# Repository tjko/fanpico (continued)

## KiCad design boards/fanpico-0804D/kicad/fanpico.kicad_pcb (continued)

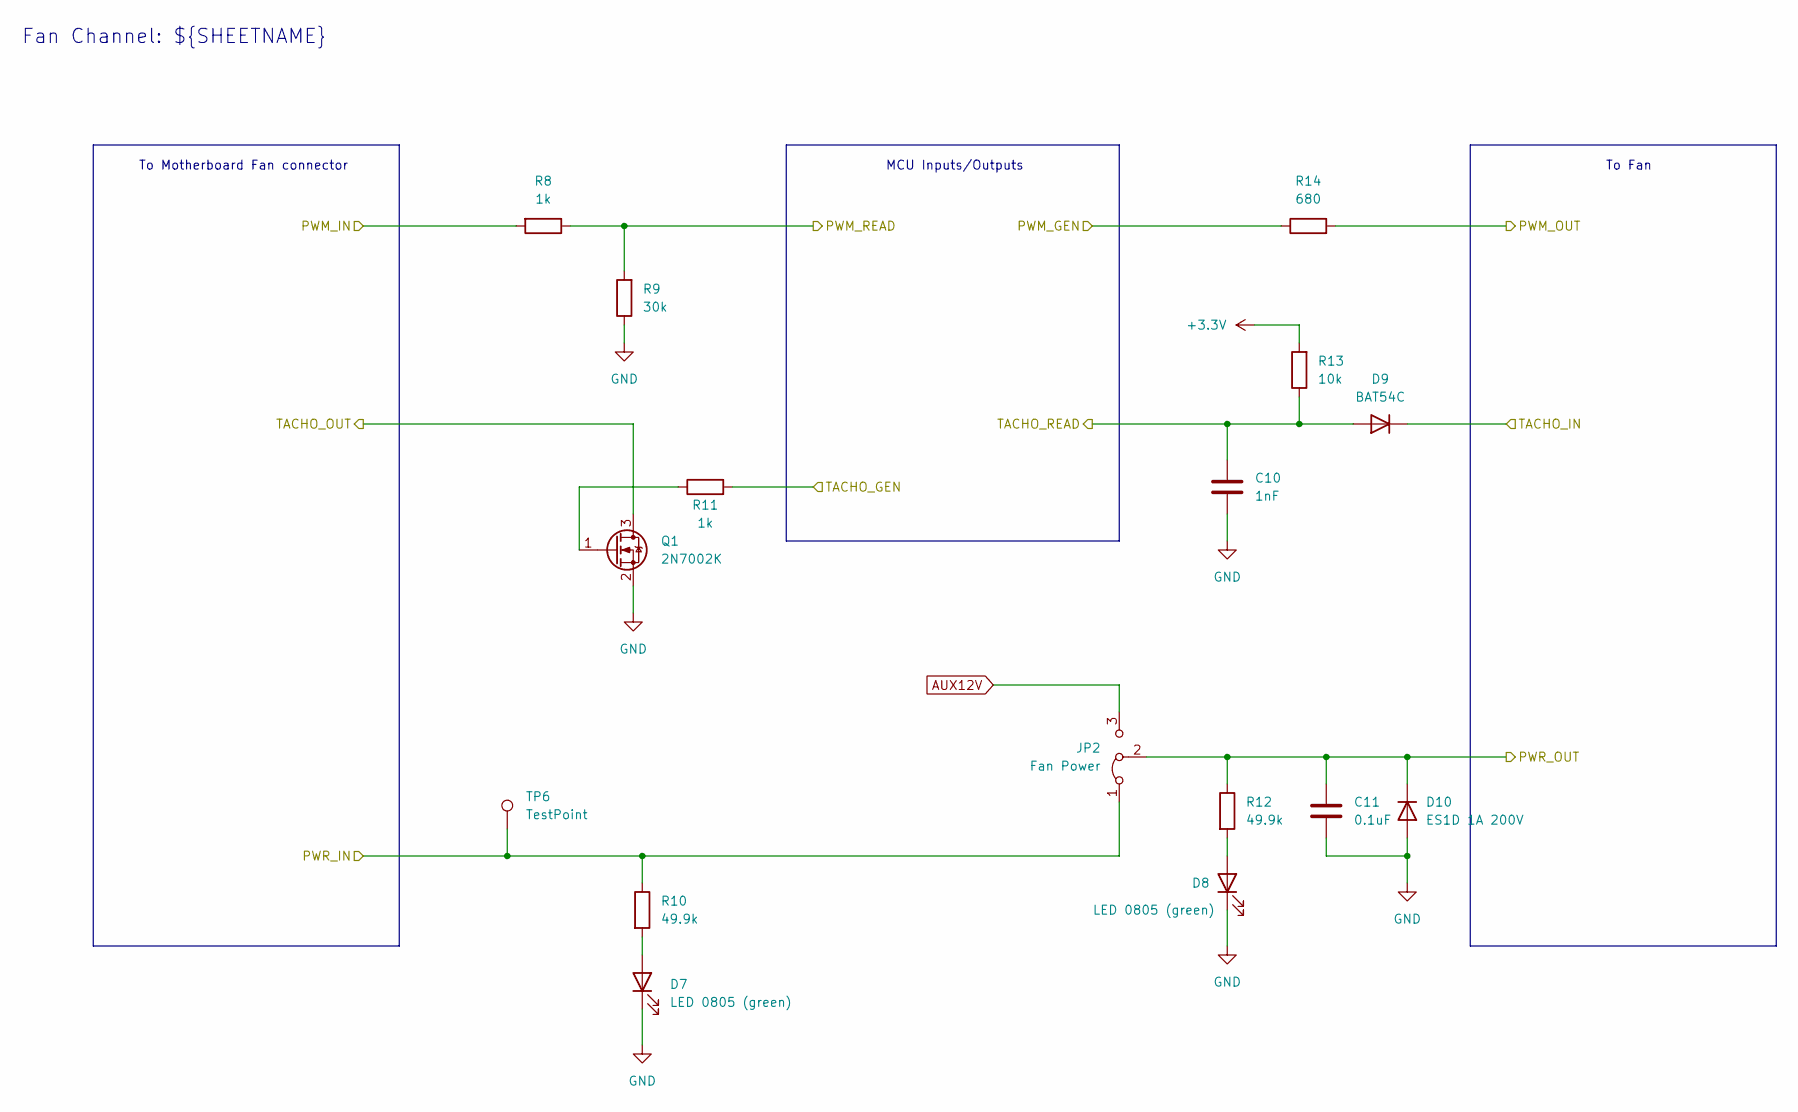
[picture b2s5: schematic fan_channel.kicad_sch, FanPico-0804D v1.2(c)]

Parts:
C10: 1nF; C_0603_1608Metric_Pad1.08x0.95mm_HandSolder; LCSC Part Number C1588
C11: 0.1uF; C_0603_1608Metric_Pad1.08x0.95mm_HandSolder; LCSC Part Number C1591
D7, D8: LED 0805 (green); LED_0805_2012Metric_Pad1.15x1.40mm_HandSolder; LCSC Part Number C434432
D9: BAT54C; D_SOT-23_ANK; LCSC Part Number C2844172
D10: ES1D 1A 200V; D_SMA_Handsoldering; LCSC Part Number C445494
JP2: Fan Power; PinHeader_1x03_P2.54mm_Vertical
Q1: 2N7002K; SOT-23; LCSC Part Number C85047
R8, R11: 1k; R_0603_1608Metric_Pad0.98x0.95mm_HandSolder; LCSC Part Number C22548
R9: 30k; R_0603_1608Metric_Pad0.98x0.95mm_HandSolder; LCSC Part Number C100001
R10, R12: 49.9k; R_0603_1608Metric_Pad0.98x0.95mm_HandSolder; LCSC Part Number C114624
R13: 10k; R_0603_1608Metric_Pad0.98x0.95mm_HandSolder; LCSC Part Number C98220
R14: 680; R_0603_1608Metric_Pad0.98x0.95mm_HandSolder; LCSC Part Number C115415
TP6: TestPoint; TestPoint_Pad_D1.5mm

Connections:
3V3: R13.2; also elsewhere on the board
/Fan Channels/Fan1/PWM_IN: R8.2; also elsewhere on the board
/Fan Channels/Fan1/PWM_OUT: R14.2; also elsewhere on the board
/Fan Channels/Fan1/PWR_OUT: C11.1, D10.1 (K), JP2.2 (C), R12.1; also elsewhere on the board
/Fan Channels/Fan1/TACHO_IN: D9.1 (K); also elsewhere on the board
/Fan Channels/Fan1/TACHO_OUT: Q1.3 (D); also elsewhere on the board
AUX12V: JP2.3 (B); also elsewhere on the board
FAN1_PWM_GEN: R14.1; also elsewhere on the board
FAN1_PWR: JP2.1 (A), R10.1; also elsewhere on the board
FAN1_TACHO_READ: C10.1, D9.2 (A), R13.1; also elsewhere on the board
GND: C10.2, C11.2, D7.1 (K), D8.1 (K), D10.2 (A), Q1.2 (S), R9.1; also elsewhere on the board
MBFAN1_PWM_READ: R8.1, R9.2; also elsewhere on the board
MBFAN1_TACHO_GEN: R11.2; also elsewhere on the board
unnamed: D7.2 (A), R10.2
unnamed: D8.2 (A), R12.2
unnamed: Q1.1 (G), R11.1

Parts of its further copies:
C13, C16, C19: 1nF; C_0603_1608Metric_Pad1.08x0.95mm_HandSolder; LCSC Part Number C1588
C14, C17, C20: 0.1uF; C_0603_1608Metric_Pad1.08x0.95mm_HandSolder; LCSC Part Number C1591
D11, D12, D15, D16, D19, D20: LED 0805 (green); LED_0805_2012Metric_Pad1.15x1.40mm_HandSolder; LCSC Part Number C434432
D13, D17, D21: BAT54C; D_SOT-23_ANK; LCSC Part Number C2844172
D14, D18, D22: ES1D 1A 200V; D_SMA_Handsoldering; LCSC Part Number C445494
JP3, JP4, JP5: Fan Power; PinHeader_1x03_P2.54mm_Vertical
Q2, Q3, Q4: 2N7002K; SOT-23; LCSC Part Number C85047
R15, R18, R22, R25, R29, R32: 1k; R_0603_1608Metric_Pad0.98x0.95mm_HandSolder; LCSC Part Number C22548
R16, R23, R30: 30k; R_0603_1608Metric_Pad0.98x0.95mm_HandSolder; LCSC Part Number C100001
R17, R19, R24, R26, R31, R33: 49.9k; R_0603_1608Metric_Pad0.98x0.95mm_HandSolder; LCSC Part Number C114624
R20, R27, R34: 10k; R_0603_1608Metric_Pad0.98x0.95mm_HandSolder; LCSC Part Number C98220
R21, R28, R35: 680; R_0603_1608Metric_Pad0.98x0.95mm_HandSolder; LCSC Part Number C115415

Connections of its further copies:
3V3: R20.2, R27.2, R34.2; also elsewhere on the board
/Fan Channels/Fan2/PWM_IN: R15.2; also elsewhere on the board
/Fan Channels/Fan2/PWM_OUT: R21.2; also elsewhere on the board
/Fan Channels/Fan2/PWR_OUT: C14.1, D14.1 (K), JP3.2 (C), R19.1; also elsewhere on the board
/Fan Channels/Fan2/TACHO_IN: D13.1 (K); also elsewhere on the board
/Fan Channels/Fan2/TACHO_OUT: Q2.3 (D); also elsewhere on the board
/Fan Channels/Fan3/PWM_IN: R29.2; also elsewhere on the board
/Fan Channels/Fan3/PWM_OUT: R35.2; also elsewhere on the board
/Fan Channels/Fan3/PWR_OUT: C20.1, D22.1 (K), JP5.2 (C), R33.1; also elsewhere on the board
/Fan Channels/Fan3/TACHO_IN: D21.1 (K); also elsewhere on the board
/Fan Channels/Fan3/TACHO_OUT: Q4.3 (D); also elsewhere on the board
/Fan Channels/Fan4/PWM_IN: R22.2; also elsewhere on the board
/Fan Channels/Fan4/PWM_OUT: R28.2; also elsewhere on the board
/Fan Channels/Fan4/PWR_OUT: C17.1, D18.1 (K), JP4.2 (C), R26.1; also elsewhere on the board
/Fan Channels/Fan4/TACHO_IN: D17.1 (K); also elsewhere on the board
/Fan Channels/Fan4/TACHO_OUT: Q3.3 (D); also elsewhere on the board
AUX12V: JP3.3 (B), JP4.3 (B), JP5.3 (B); also elsewhere on the board
FAN2_PWM_GEN: R21.1; also elsewhere on the board
FAN2_PWR: JP3.1 (A), R17.1; also elsewhere on the board
FAN2_TACHO_READ: C13.1, D13.2 (A), R20.1; also elsewhere on the board
FAN3_PWM_GEN: R35.1; also elsewhere on the board
FAN3_PWR: JP5.1 (A), R31.1; also elsewhere on the board
FAN3_TACHO_READ: C19.1, D21.2 (A), R34.1; also elsewhere on the board
FAN4_PWM_GEN: R28.1; also elsewhere on the board
FAN4_PWR: JP4.1 (A), R24.1; also elsewhere on the board
FAN4_TACHO_READ: C16.1, D17.2 (A), R27.1; also elsewhere on the board
GND: C13.2, C14.2, C16.2, C17.2, C19.2, C20.2, D11.1 (K), D12.1 (K), D14.2 (A), D15.1 (K), D16.1 (K), D18.2 (A), D19.1 (K), D20.1 (K), D22.2 (A), Q2.2 (S), Q3.2 (S), Q4.2 (S), R16.1, R23.1, R30.1; also elsewhere on the board
MBFAN2_PWM_READ: R15.1, R16.2; also elsewhere on the board
MBFAN2_TACHO_GEN: R18.2; also elsewhere on the board
MBFAN3_PWM_READ: R29.1, R30.2; also elsewhere on the board
MBFAN3_TACHO_GEN: R32.2; also elsewhere on the board
MBFAN4_PWM_READ: R22.1, R23.2; also elsewhere on the board
MBFAN4_TACHO_GEN: R25.2; also elsewhere on the board
unnamed: D11.2 (A), R17.2
unnamed: D12.2 (A), R19.2
unnamed: D15.2 (A), R24.2
unnamed: D16.2 (A), R26.2
unnamed: D19.2 (A), R31.2
unnamed: D20.2 (A), R33.2
unnamed: Q2.1 (G), R18.1
unnamed: Q3.1 (G), R25.1
unnamed: Q4.1 (G), R32.1

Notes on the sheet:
MCU Inputs/Outputs
To Motherboard Fan connector
Fan Channel: ${SHEETNAME}
To Fan

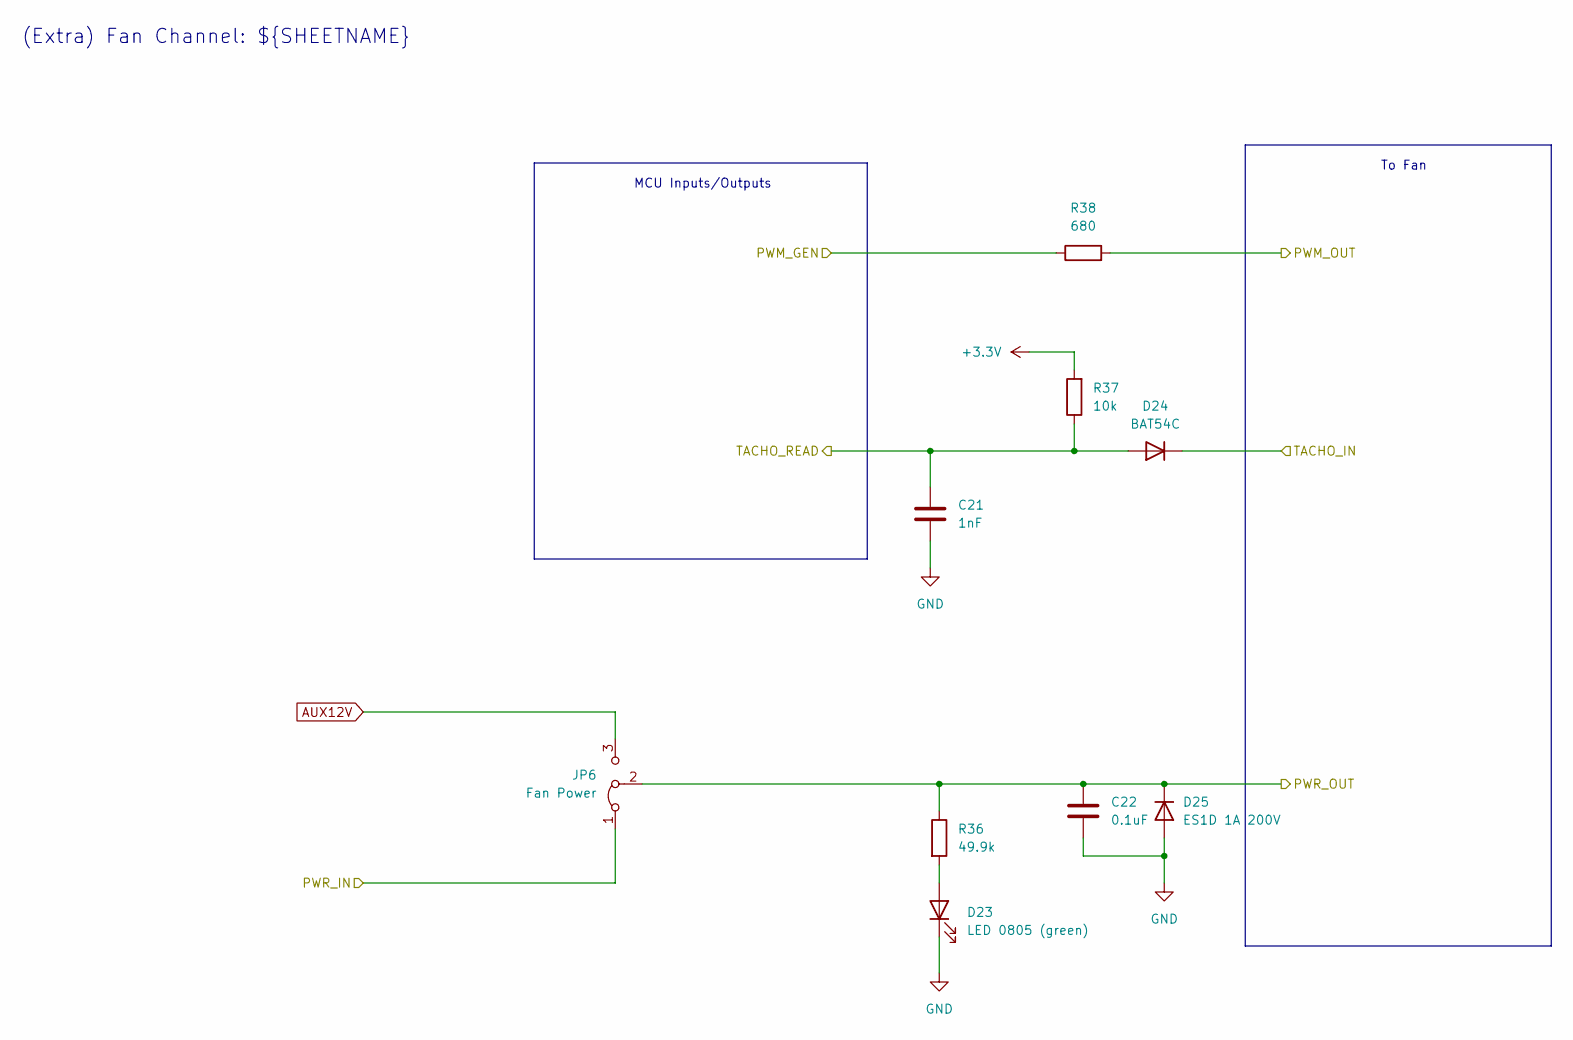
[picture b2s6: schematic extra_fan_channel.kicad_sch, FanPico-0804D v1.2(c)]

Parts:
C21: 1nF; C_0603_1608Metric_Pad1.08x0.95mm_HandSolder; LCSC Part Number C1588
C22: 0.1uF; C_0603_1608Metric_Pad1.08x0.95mm_HandSolder; LCSC Part Number C1591
D23: LED 0805 (green); LED_0805_2012Metric_Pad1.15x1.40mm_HandSolder; LCSC Part Number C434432
D24: BAT54C; D_SOT-23_ANK; LCSC Part Number C2844172
D25: ES1D 1A 200V; D_SMA_Handsoldering; LCSC Part Number C445494
JP6: Fan Power; PinHeader_1x03_P2.54mm_Vertical
R36: 49.9k; R_0603_1608Metric_Pad0.98x0.95mm_HandSolder; LCSC Part Number C114624
R37: 10k; R_0603_1608Metric_Pad0.98x0.95mm_HandSolder; LCSC Part Number C98220
R38: 680; R_0603_1608Metric_Pad0.98x0.95mm_HandSolder; LCSC Part Number C115415

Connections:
3V3: R37.2; also elsewhere on the board
/Fan Channels/Fan5/PWM_OUT: R38.2; also elsewhere on the board
/Fan Channels/Fan5/PWR_OUT: C22.1, D25.1 (K), JP6.2 (C), R36.1; also elsewhere on the board
/Fan Channels/Fan5/TACHO_IN: D24.1 (K); also elsewhere on the board
AUX12V: JP6.3 (B); also elsewhere on the board
FAN1_PWR: JP6.1 (A); also elsewhere on the board
FAN5_PWM_GEN: R38.1; also elsewhere on the board
FAN5_TACHO_READ: C21.1, D24.2 (A), R37.1; also elsewhere on the board
GND: C21.2, C22.2, D23.1 (K), D25.2 (A); also elsewhere on the board
unnamed: D23.2 (A), R36.2

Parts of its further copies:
C23, C25, C27: 1nF; C_0603_1608Metric_Pad1.08x0.95mm_HandSolder; LCSC Part Number C1588
C24, C26, C28: 0.1uF; C_0603_1608Metric_Pad1.08x0.95mm_HandSolder; LCSC Part Number C1591
D26, D29, D32: LED 0805 (green); LED_0805_2012Metric_Pad1.15x1.40mm_HandSolder; LCSC Part Number C434432
D27, D30, D33: BAT54C; D_SOT-23_ANK; LCSC Part Number C2844172
D28, D31, D34: ES1D 1A 200V; D_SMA_Handsoldering; LCSC Part Number C445494
JP7, JP8, JP9: Fan Power; PinHeader_1x03_P2.54mm_Vertical
R39, R42, R45: 49.9k; R_0603_1608Metric_Pad0.98x0.95mm_HandSolder; LCSC Part Number C114624
R40, R43, R46: 10k; R_0603_1608Metric_Pad0.98x0.95mm_HandSolder; LCSC Part Number C98220
R41, R44, R47: 680; R_0603_1608Metric_Pad0.98x0.95mm_HandSolder; LCSC Part Number C115415

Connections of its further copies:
3V3: R40.2, R43.2, R46.2; also elsewhere on the board
/Fan Channels/Fan6/PWM_OUT: R41.2; also elsewhere on the board
/Fan Channels/Fan6/PWR_OUT: C24.1, D28.1 (K), JP7.2 (C), R39.1; also elsewhere on the board
/Fan Channels/Fan6/TACHO_IN: D27.1 (K); also elsewhere on the board
/Fan Channels/Fan7/PWM_OUT: R44.2; also elsewhere on the board
/Fan Channels/Fan7/PWR_OUT: C26.1, D31.1 (K), JP8.2 (C), R42.1; also elsewhere on the board
/Fan Channels/Fan7/TACHO_IN: D30.1 (K); also elsewhere on the board
/Fan Channels/Fan8/PWM_OUT: R47.2; also elsewhere on the board
/Fan Channels/Fan8/PWR_OUT: C28.1, D34.1 (K), JP9.2 (C), R45.1; also elsewhere on the board
/Fan Channels/Fan8/TACHO_IN: D33.1 (K); also elsewhere on the board
AUX12V: JP7.3 (B), JP8.3 (B), JP9.3 (B); also elsewhere on the board
FAN2_PWR: JP7.1 (A); also elsewhere on the board
FAN3_PWR: JP8.1 (A); also elsewhere on the board
FAN4_PWR: JP9.1 (A); also elsewhere on the board
FAN6_PWM_GEN: R41.1; also elsewhere on the board
FAN6_TACHO_READ: C23.1, D27.2 (A), R40.1; also elsewhere on the board
FAN7_PWM_GEN: R44.1; also elsewhere on the board
FAN7_TACHO_READ: C25.1, D30.2 (A), R43.1; also elsewhere on the board
FAN8_PWM_GEN: R47.1; also elsewhere on the board
FAN8_TACHO_READ: C27.1, D33.2 (A), R46.1; also elsewhere on the board
GND: C23.2, C24.2, C25.2, C26.2, C27.2, C28.2, D26.1 (K), D28.2 (A), D29.1 (K), D31.2 (A), D32.1 (K), D34.2 (A); also elsewhere on the board
unnamed: D26.2 (A), R39.2
unnamed: D29.2 (A), R42.2
unnamed: D32.2 (A), R45.2

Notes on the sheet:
MCU Inputs/Outputs
(Extra) Fan Channel: ${SHEETNAME}
To Fan

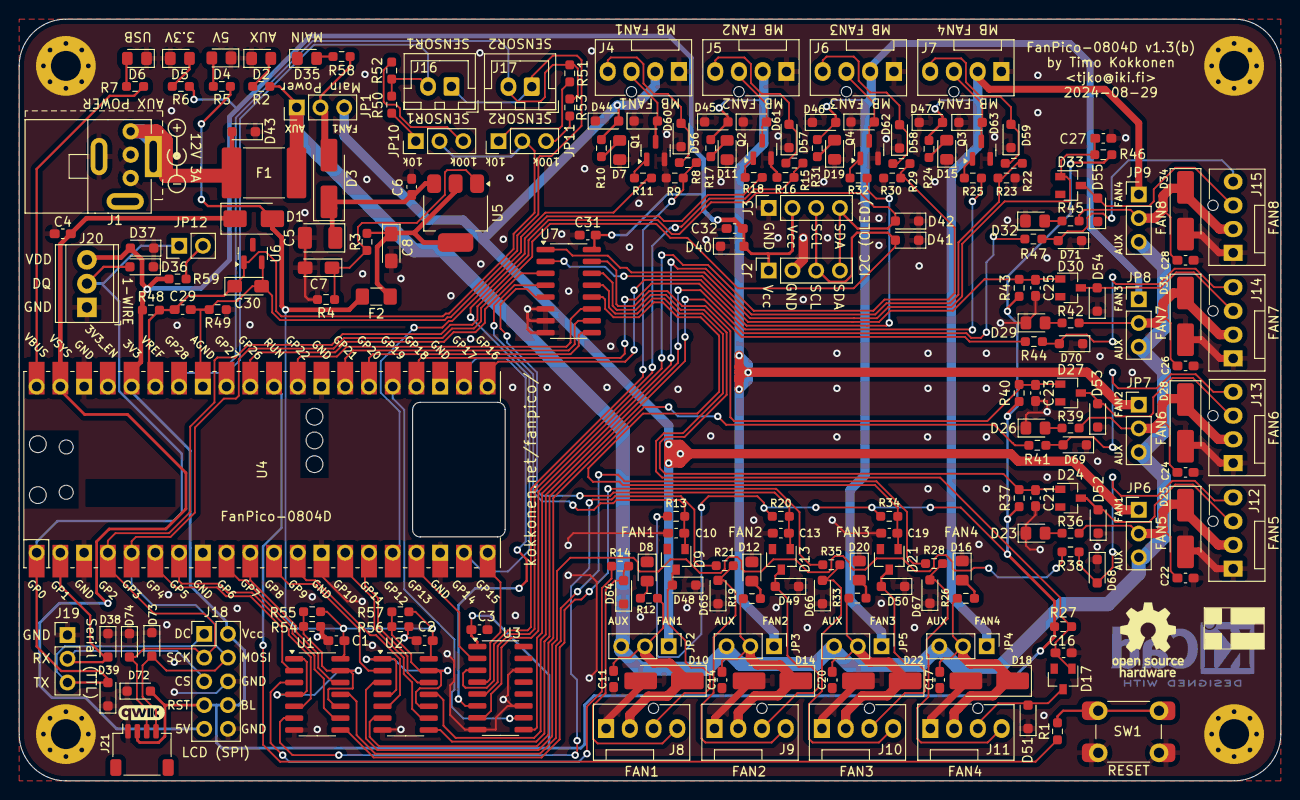
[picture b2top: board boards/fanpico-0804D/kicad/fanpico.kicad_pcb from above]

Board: 2 copper layers, 135.0 x 81.5 mm, 213 parts (0 on the bottom side), 125 nets.

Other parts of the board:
D44, D45, D46, D47, D48, D49, D50, D51, D52, D53, D54, D55, D60, D61, D62, D63: 12V TVS; D_SOD-323_HandSoldering
D56, D57, D58, D59, D64, D65, D66, D67, D68, D69, D70, D71: 5V TVS; D_SOD-323_HandSoldering
G1: qwiic_Logo; qwiic_5mm

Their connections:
/Fan Channels/Fan1/PWM_IN: D56.2 (A2); also elsewhere on the board
/Fan Channels/Fan1/PWM_OUT: D64.2 (A2); also elsewhere on the board
/Fan Channels/Fan1/TACHO_IN: D48.2 (A2); also elsewhere on the board
/Fan Channels/Fan1/TACHO_OUT: D60.2 (A2); also elsewhere on the board
/Fan Channels/Fan2/PWM_IN: D57.2 (A2); also elsewhere on the board
/Fan Channels/Fan2/PWM_OUT: D65.2 (A2); also elsewhere on the board
/Fan Channels/Fan2/TACHO_IN: D49.2 (A2); also elsewhere on the board
/Fan Channels/Fan2/TACHO_OUT: D61.2 (A2); also elsewhere on the board
/Fan Channels/Fan3/PWM_IN: D58.2 (A2); also elsewhere on the board
/Fan Channels/Fan3/PWM_OUT: D66.2 (A2); also elsewhere on the board
/Fan Channels/Fan3/TACHO_IN: D50.2 (A2); also elsewhere on the board
/Fan Channels/Fan3/TACHO_OUT: D62.2 (A2); also elsewhere on the board
/Fan Channels/Fan4/PWM_IN: D59.2 (A2); also elsewhere on the board
/Fan Channels/Fan4/PWM_OUT: D67.2 (A2); also elsewhere on the board
/Fan Channels/Fan4/TACHO_IN: D51.2 (A2); also elsewhere on the board
/Fan Channels/Fan4/TACHO_OUT: D63.2 (A2); also elsewhere on the board
/Fan Channels/Fan5/PWM_OUT: D68.2 (A2); also elsewhere on the board
/Fan Channels/Fan5/TACHO_IN: D52.2 (A2); also elsewhere on the board
/Fan Channels/Fan6/PWM_OUT: D69.2 (A2); also elsewhere on the board
/Fan Channels/Fan6/TACHO_IN: D53.2 (A2); also elsewhere on the board
/Fan Channels/Fan7/PWM_OUT: D70.2 (A2); also elsewhere on the board
/Fan Channels/Fan7/TACHO_IN: D54.2 (A2); also elsewhere on the board
/Fan Channels/Fan8/PWM_OUT: D71.2 (A2); also elsewhere on the board
/Fan Channels/Fan8/TACHO_IN: D55.2 (A2); also elsewhere on the board
FAN1_PWR: D44.2 (A2); also elsewhere on the board
FAN2_PWR: D45.2 (A2); also elsewhere on the board
FAN3_PWR: D46.2 (A2); also elsewhere on the board
FAN4_PWR: D47.2 (A2); also elsewhere on the board
GND: D44.1 (A1), D45.1 (A1), D46.1 (A1), D47.1 (A1), D48.1 (A1), D49.1 (A1), D50.1 (A1), D51.1 (A1), D52.1 (A1), D53.1 (A1), D54.1 (A1), D55.1 (A1), D56.1 (A1), D57.1 (A1), D58.1 (A1), D59.1 (A1), D60.1 (A1), D61.1 (A1), D62.1 (A1), D63.1 (A1), D64.1 (A1), D65.1 (A1), D66.1 (A1), D67.1 (A1), D68.1 (A1), D69.1 (A1), D70.1 (A1), D71.1 (A1); also elsewhere on the board

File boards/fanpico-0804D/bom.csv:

Ref,Qnty,Value,Cmp name,Footprint,Description,Vendor,Mouser P/N,LCSC P/N
"C1, C2, C3, C4, C6, C11, C14, C17, C20, C22, C24, C26, C28, C29, C31, C32",16,0.1uF,C_Small,Capacitor_SMD:C_0603_1608Metric_Pad1.08x0.95mm_HandSolder,"Unpolarized capacitor, small symbol",,,C1591
"C5,",1,10uF 25V,C Tantalum,Capacitor_Tantalum_SMD:CP_EIA-3528-12_Kemet-T_Pad1.50x2.35mm_HandSolder,"Polarized capacitor, small symbol",,,C110053 or C7194
"C7, C8, C30",3,10uF 16V,C Tantalum,Capacitor_Tantalum_SMD:CP_EIA-3216-18_Kemet-A_Pad1.58x1.35mm_HandSolder,Polarized capacitor,,80--T491A106K016,C7171
"C10, C13, C16, C19, C21, C23, C25, C27,",8,1nF,C,Capacitor_SMD:C_0603_1608Metric_Pad1.08x0.95mm_HandSolder,Unpolarized capacitor,,,C1588
"D1,",1,SM5819PL 1A 40V,D_Schottky,Diode_SMD:D_SMA,Schottky diode,,833-SM5819PL-TP,C669023
"D2, D4, D5, D6, D7, D8, D11, D12, D15, D16, D19, D20, D23, D26, D29, D32,",16,LED 0805 (green),LED,LED_SMD:LED_0805_2012Metric_Pad1.15x1.40mm_HandSolder,Light emitting diode,,710-150080GS75000,C434432
"D3, D10, D14, D18, D22, D25, D28, D31, D34,",9,ES1D 1A 200V,D,Diode_SMD:D_SMA_Handsoldering,Diode,,512-ES1D,C445494
"D9, D13, D17, D21, D24, D27, D30, D33,",8,BAT54C,D,Diode_SMD:D_SOT-23_ANK,Diode,,241-BAT54C_R1_00001,C2992451 or C2844172
"F1,",1,Polyfuse 3A,Polyfuse,Fuse:Fuse_2920_7451Metric_Pad2.10x5.45mm_HandSolder,"Resettable fuse, polymeric positive temperature coefficient",,530-0ZCF0300BF2C,C20829 or C2977527
"F2,",1,Polyfuse 0.5A,Polyfuse,Fuse:Fuse_1206_3216Metric_Pad1.42x1.75mm_HandSolder,"Resettable fuse, polymeric positive temperature coefficient",,530-0ZCJ0050AF2E,C70072
"J1,",1,171826-4,Berg Connector,Connector_TE-Connectivity:TE 171826-4 Floppy 4-pin,Floppy Power Connector,TE,571-1718264,C590635
"J2, J3",2,Header,Header,Connector_PinSocket_2.54mm:PinSocket_1x04_P2.54mm_Vertical,Header 2.54mm,,,C2935910
J4 - J15,12,47053-1000,4-pin Fan Connector,Connector:FanPinHeader_1x04_P2.54mm_Vertical,PC 4-pin (PWM) fan connector,Molex,538-47053-1000,C240840
"J16, J17",2,JST-XH,2-pin JST XH 2.5mm,Connector_JST:JST_XH_B2B-XH-A_1x02_P2.50mm_Vertical,2-pin connector,,,C158012
J18,1,Header,Header,Connector_PinHeader_2.54mm:PinHeader_2x05_P2.54mm_Vertical,Header 2.54mm,,,C492422
"JP1 - JP11, J19",11,Header,Header,Connector_PinHeader_2.54mm:PinHeader_1x03_P2.54mm_Vertical,Header 2.54mm,,,C124376
JP1 - JP11,11,Jumper,Jumper_3_Bridged12,Connector_PinHeader_2.54mm:PinHeader_1x03_P2.54mm_Vertical,Jumper 2.54mm,,,C5305
"Q1, Q2, Q3, Q4,",4,2N7002K,2N7002K,Package_TO_SOT_SMD:SOT-23,"0.38A Id, 60V Vds, N-Channel MOSFET, SOT-23",,512-2N7002K,C85047
"R1, R4, R8, R11, R15, R18, R22, R25, R29, R32,",10,1k,R,Resistor_SMD:R_0603_1608Metric_Pad0.98x0.95mm_HandSolder,Resistor,,,C22548
"R2, R10, R12, R17, R19, R24, R26, R31, R33, R36, R39, R42, R45,",13,49.9k,R,Resistor_SMD:R_0603_1608Metric_Pad0.98x0.95mm_HandSolder,Resistor,,,C114624
"R3, R48,",2,330,R,Resistor_SMD:R_0603_1608Metric_Pad0.98x0.95mm_HandSolder,Resistor,,,C105881
"R5, R7, R13, R20, R27, R34, R37, R40, R43, R46, R50, R51,",12,10k,R,Resistor_SMD:R_0603_1608Metric_Pad0.98x0.95mm_HandSolder,Resistor,,,C98220
"R6,",1,4.99k,R,Resistor_SMD:R_0603_1608Metric_Pad0.98x0.95mm_HandSolder,Resistor,,,C114621
"R9, R16, R23, R30,",4,30k,R,Resistor_SMD:R_0603_1608Metric_Pad0.98x0.95mm_HandSolder,Resistor,,,C100001
"R14, R21, R28, R35, R38, R41, R44, R47,",8,680,R,Resistor_SMD:R_0603_1608Metric_Pad0.98x0.95mm_HandSolder,Resistor,,,C115415
"R49, R55, R57",3,0,R,Resistor_SMD:R_0603_1608Metric_Pad0.98x0.95mm_HandSolder,Resistor,,,C100044 or C21189
"R52, R53",2,100k,R,Resistor_SMD:R_0603_1608Metric_Pad0.98x0.95mm_HandSolder,Resistor,,,C14675
SW1,1,SW_Push,SW_Push,Button_Switch_THT:SW_PUSH_6mm_SMD_2,"Push button switch, generic, two pins",,,C221880
"U1, U2",2,SN74AHCT126,SN74AHCT126,Package_SO:SOIC-14_3.9x8.7mm_P1.27mm,Low (3.3V) to High (5V) TTL level converter,TI,,C163728
U3,1,CD74HC4050NSR,CD74HC4050M,Package_SO:SOIC-16_3.9x9.9mm_P1.27mm,High (5-12V) to Low (3.3V) TTL level converter,TI,,C131932
U4,1,Pico / Pico W,Pico,MCU_RaspberryPi_and_Boards:RPi_Pico_SMD_TH,Raspberry Pi Pico,RPi,474-DEV-17829,
U5,1,SPX1117-ADJ,LM1117-ADJ,Package_TO_SOT_SMD:SOT-223,"800mA Low-Dropout Linear Regulator, adjustable output, TO-220/TO-252/TO-263/SOT-223",Maxim,701-SPX1117M3-L/TR,C67402
U6,1,LM4040BIM3-3.0,LM4040 3.0V,Package_TO_SOT_SMD:SOT-23,"3.000V Precision Micropower Shunt Voltage Reference, SOT-23",,926-LM4040BIM330NOPB,C143326
U7,1,74HC4051,74HC4051,Package_SO:SOIC-16_3.9x9.9mm_P1.27mm,"8-channel analog multiplexer/demultiplexer, DIP-16/SOIC-16/TSSOP-16",,771-74HC4051D-T,C9386

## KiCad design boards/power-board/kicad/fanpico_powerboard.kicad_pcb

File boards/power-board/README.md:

# FanPico PowerBoard

PCB Size: 65mm x 65mm

This is a small power injector board for powering high-power fans, that require
too much current to be connected directly into Fan ports on FanPico boards.

Board is meant to sit in between FanPico Fan ports and the high-power fans.

Fan Power Supply (12V) should be connected into one of the power inputs (only on input
should be used at a time). Fans should be connected into "FAN" ports on the board, and
cables connected from "FANCTRL" ports into FanPico (FAN ports) for fan control/monitoring.

Note, "FANCTRL" ports do not have voltage pin connected, so no power is drawn from the fan controller.

## Assembly note
Install either F1 (polyfuse) or F2 (fuse holder for 5x20mm fuses), not both.

## Manufacturing note
PCB should have at least 2oz copper thickness for adequate current carrying capacity.

## Change Log

- v1.1
  - Make tracks thicker for ground pins on power connectors.
- v1.0 
  - Initial revision.

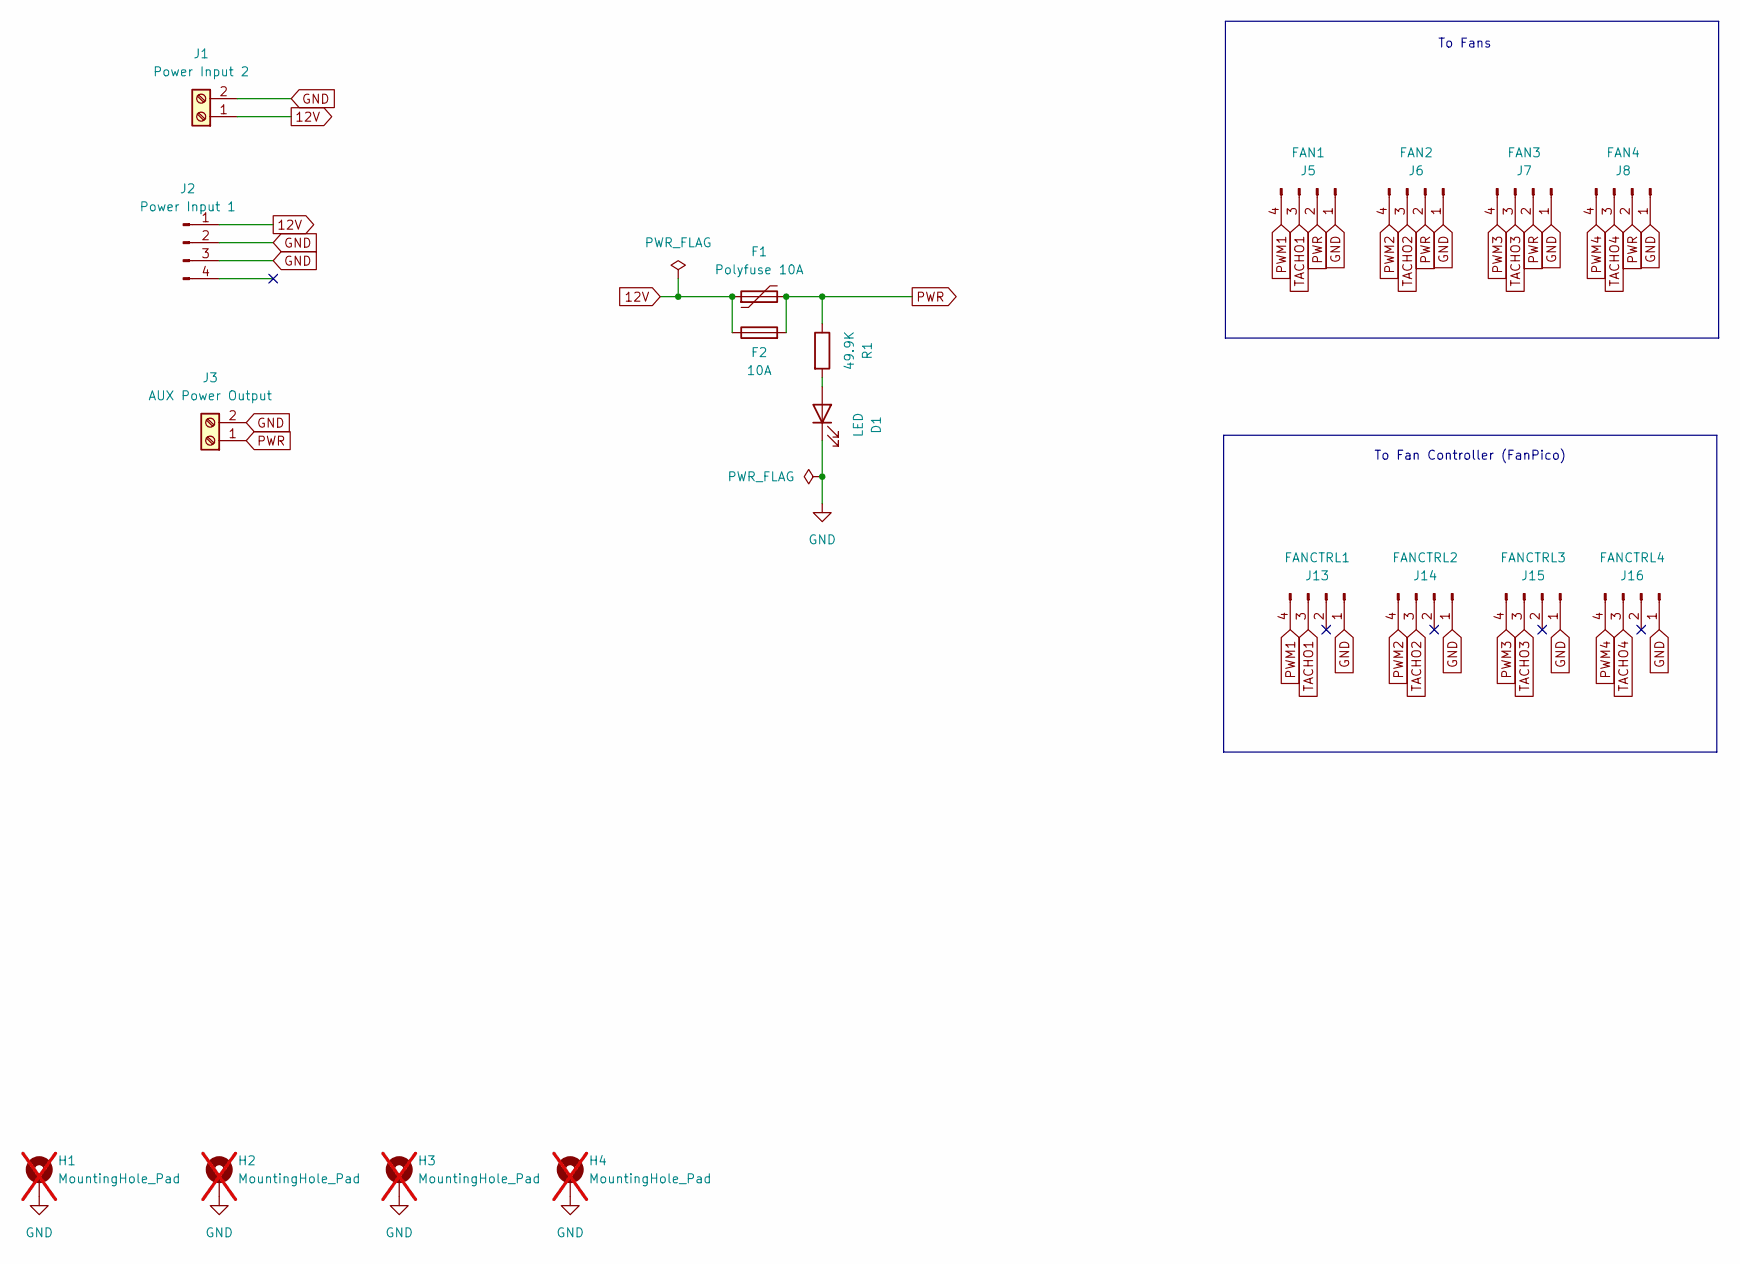
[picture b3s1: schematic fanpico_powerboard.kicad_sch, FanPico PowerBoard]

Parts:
D1: LED; D_0805_2012Metric_Pad1.15x1.40mm_HandSolder; Mouser Part Number 710-150080GS75000; LCSC Part Number C434432
F1: Polyfuse 10A; Fuse_2920_7451Metric_Pad2.10x5.45mm_HandSolder; LCSC Part Number C22446882
F2: 10A; Fuseholder_Clip-5x20mm_Littelfuse_445-030_Inline_P20.50x5.2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; LCSC Part Number C717027
H1, H2, H3, H4: MountingHole_Pad; MountingHole_3.2mm_M3_Pad_Via; not fitted
J1: Power Input 2; TerminalBlock_Phoenix_MKDS-1,5-2_1x02_P5.00mm_Horizontal; LCSC Part Number C1509679
J2: Power Input 1; TE_MATE-N-LOK_350211-1_1x04_P5.08mm_Vertical_and_RightAngle; Mouser Part Number 571-3502111 / 571-1748041; LCSC Part Number C305826 or C7461144
J3: AUX Power Output; TerminalBlock_Phoenix_MKDS-1,5-2_1x02_P5.00mm_Horizontal; LCSC Part Number C1509679
J5: FAN1; FanPinHeader_1x04_P2.54mm_Vertical; Mouser Part Number 538-47053-1000; LCSC Part Number C240840
J6: FAN2; FanPinHeader_1x04_P2.54mm_Vertical; Mouser Part Number 538-47053-1000; LCSC Part Number C240840
J7: FAN3; FanPinHeader_1x04_P2.54mm_Vertical; Mouser Part Number 538-47053-1000; LCSC Part Number C240840
J8: FAN4; FanPinHeader_1x04_P2.54mm_Vertical; Mouser Part Number 538-47053-1000; LCSC Part Number C240840
J13: FANCTRL1; FanPinHeader_1x04_P2.54mm_Vertical; Mouser Part Number 538-47053-1000; LCSC Part Number C240840
J14: FANCTRL2; FanPinHeader_1x04_P2.54mm_Vertical; Mouser Part Number 538-47053-1000; LCSC Part Number C240840
J15: FANCTRL3; FanPinHeader_1x04_P2.54mm_Vertical; Mouser Part Number 538-47053-1000; LCSC Part Number C240840
J16: FANCTRL4; FanPinHeader_1x04_P2.54mm_Vertical; Mouser Part Number 538-47053-1000; LCSC Part Number C240840
R1: 49.9K; R_0603_1608Metric_Pad0.98x0.95mm_HandSolder; LCSC Part Number C114624

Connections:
12V: F1.1, F2.1, J1.1, J2.1
GND: D1.1 (K), H1.1, H2.1, H3.1, H4.1, J1.2, J2.2, J2.3, J3.2, J5.1, J6.1, J7.1, J8.1, J13.1, J14.1, J15.1, J16.1
unnamed: D1.2 (A), R1.2
PWM1: J5.4, J13.4
PWM2: J6.4, J14.4
PWM3: J7.4, J15.4
PWM4: J8.4, J16.4
PWR: F1.2, F2.2, J3.1, J5.2, J6.2, J7.2, J8.2, R1.1
TACHO1: J5.3, J13.3
TACHO2: J6.3, J14.3
TACHO3: J7.3, J15.3
TACHO4: J8.3, J16.3

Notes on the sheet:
To Fans
To Fan Controller (FanPico)

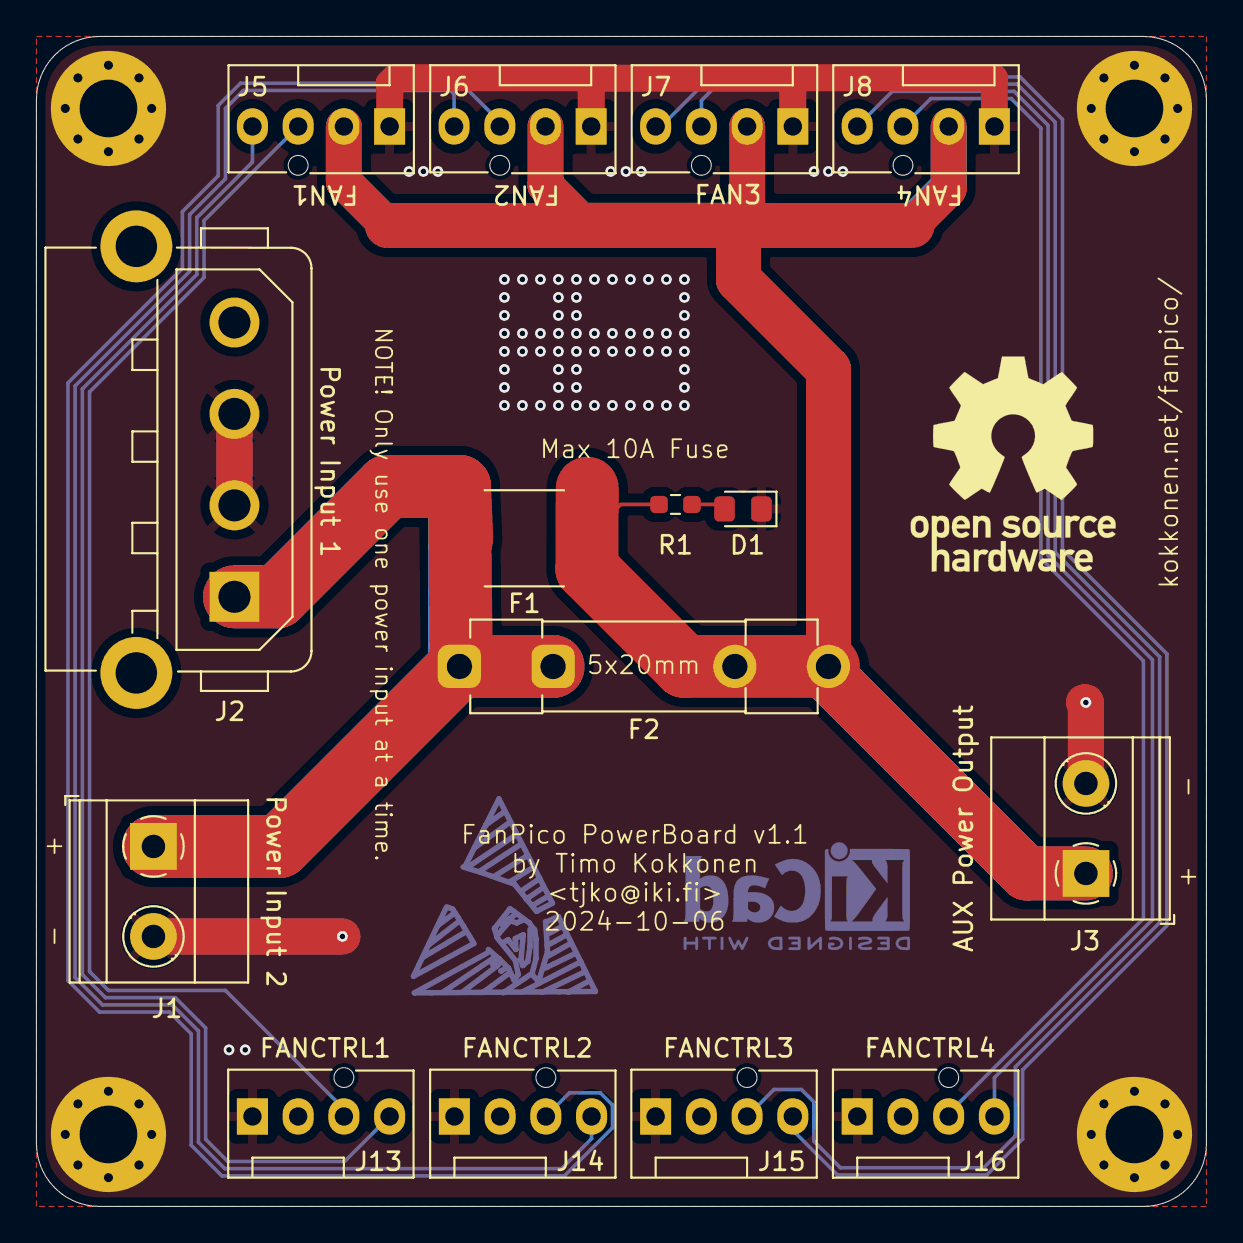
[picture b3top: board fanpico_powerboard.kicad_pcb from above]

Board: 2 copper layers, 65.0 x 65.0 mm, 19 parts (0 on the bottom side), 12 nets.

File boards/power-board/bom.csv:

"Reference","Value","Datasheet","Footprint","Qty","DNP","LCSC Part Number","Mouser Part Number"
"D1","LED","~","Diode_SMD:D_0805_2012Metric_Pad1.15x1.40mm_HandSolder","1","","C434432","710-150080GS75000"
"F1","Polyfuse 10A","~","Fuse:Fuse_2920_7451Metric_Pad2.10x5.45mm_HandSolder","1","","C22446882",""
"F2","10A","~","FanPico:Fuseholder_Clip-5x20mm_Littelfuse_445-030_Inline_P20.50x5.20mm_D1.30mm_Horizontal","1","","C717027",""
"J1","Power Input 2","~","TerminalBlock_Phoenix:TerminalBlock_Phoenix_MKDS-1,5-2_1x02_P5.00mm_Horizontal","1","","C1509679",""
"J2","Power Input 1","~","FanPico:TE_MATE-N-LOK_350211-1_1x04_P5.08mm_Vertical_and_RightAngle","1","","C305826 or C7461144","571-3502111 / 571-1748041"
"J3","AUX Power Output","~","TerminalBlock_Phoenix:TerminalBlock_Phoenix_MKDS-1,5-2_1x02_P5.00mm_Horizontal","1","","C1509679",""
"J5","FAN1","~","Connector:FanPinHeader_1x04_P2.54mm_Vertical","1","","C240840","538-47053-1000"
"J6","FAN2","~","Connector:FanPinHeader_1x04_P2.54mm_Vertical","1","","C240840","538-47053-1000"
"J7","FAN3","~","Connector:FanPinHeader_1x04_P2.54mm_Vertical","1","","C240840","538-47053-1000"
"J8","FAN4","~","Connector:FanPinHeader_1x04_P2.54mm_Vertical","1","","C240840","538-47053-1000"
"J13","FANCTRL1","~","Connector:FanPinHeader_1x04_P2.54mm_Vertical","1","","C240840","538-47053-1000"
"J14","FANCTRL2","~","Connector:FanPinHeader_1x04_P2.54mm_Vertical","1","","C240840","538-47053-1000"
"J15","FANCTRL3","~","Connector:FanPinHeader_1x04_P2.54mm_Vertical","1","","C240840","538-47053-1000"
"J16","FANCTRL4","~","Connector:FanPinHeader_1x04_P2.54mm_Vertical","1","","C240840","538-47053-1000"
"R1","49.9K","~","Resistor_SMD:R_0603_1608Metric_Pad0.98x0.95mm_HandSolder","1","","C114624",""

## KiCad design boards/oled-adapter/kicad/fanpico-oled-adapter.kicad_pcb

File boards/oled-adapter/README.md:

# FanPico-OLED-Adapter

PCB Size: 25mm x 14.5mm

This is small adapter for making it easier to mount larger 1.5" 128x128 pixel OLED modules.

J1 is meant to be connected to FanPico J3 connector, then connecting OLED module to J2 (or J3).

## Change Log

v1.0 
- Initial revision.

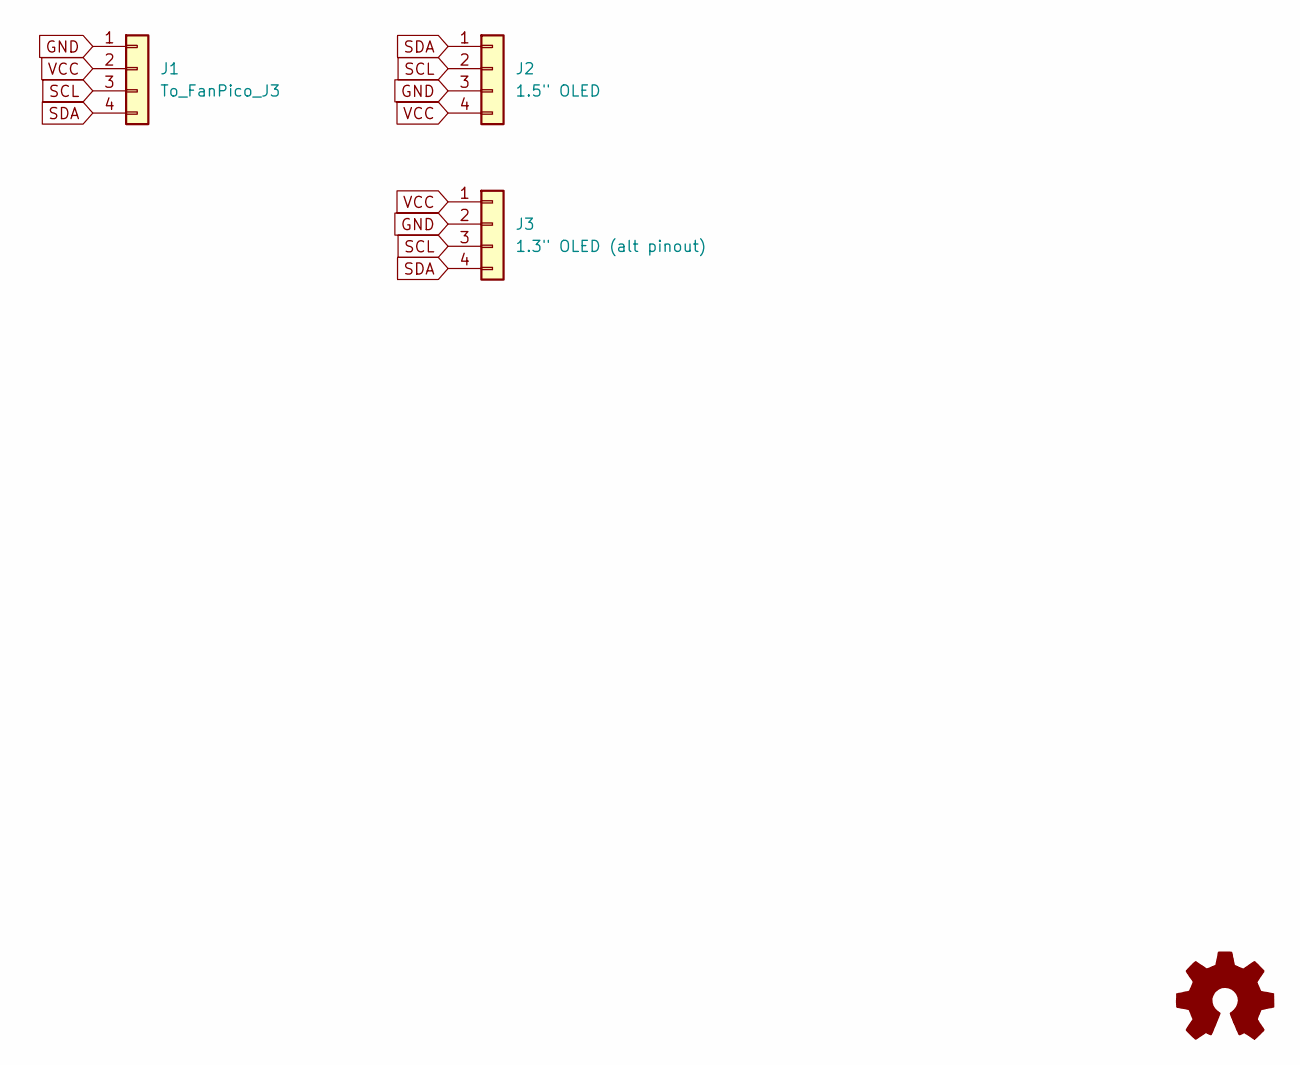
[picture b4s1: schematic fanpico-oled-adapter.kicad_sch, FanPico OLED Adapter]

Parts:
J1: To_FanPico_J3; PinHeader_1x04_P2.54mm_Vertical
J2: 1.5" OLED; PinHeader_1x04_P2.54mm_Vertical
J3: 1.3" OLED (alt pinout); PinHeader_1x04_P2.54mm_Vertical

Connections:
GND: J1.1, J2.3, J3.2
SCL: J1.3, J2.2, J3.3
SDA: J1.4, J2.1, J3.4
VCC: J1.2, J2.4, J3.1

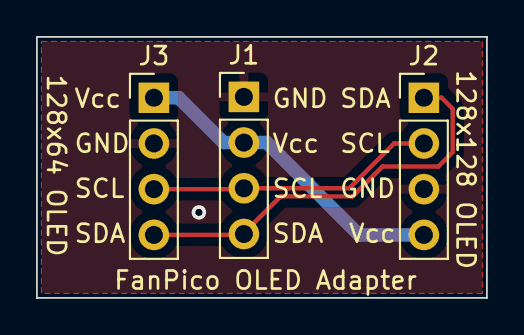
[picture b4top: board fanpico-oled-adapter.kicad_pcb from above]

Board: 2 copper layers, 25.0 x 14.5 mm, 3 parts (0 on the bottom side), 4 nets.
